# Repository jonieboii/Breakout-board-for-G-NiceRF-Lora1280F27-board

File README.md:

# Legal Disclaimer:
USER BEWARE. This is a simple breakout board created as an aid for my own prototyping purposes. 
Not withstanding the preceding and the above, DOWNLOAD, OR USE **SOLELY AT YOUR OWN RISK**. 
No warranty or representation is offered, nor should any be implied, of any kind, whatsoever. 
It is the end user's responsibility to determine suitability for their needs, and it is the end user's responsibility to test accordingly. 
Be sure to comply with all applicable rules and regulations that may govern its possession or use, which may vary by country. 
No recommendation is being made that you use it. No assistance is promised, nor should any assistance be assumed. 
No updates or corrections are promised, nor should any updates or corrections be assumed.

# G-NiceRF LoRa1280F27 Breakout Board

This is a simple breakout board for the **G-NiceRF LoRa1280F27** 500mW 2.4GHz LoRa module. Please note that this breakout board is not for the  Lora1280F27-TCXO variant which is also produced by G-Nice RF.

## Features
I have Breaken out all 18 pins from the module to standard 2.54mm headers and included two decoupling capacitors (10uF and 100nF) near VCC for stable operation.
I also  did a  **50-ohm coplanar waveguide** trace for the antenna and has inlcuded footprint for a standard **U.FL connector** for easily connecting the antennas.
The module has a full ground plane on both the top and bottom layers with stitching vias for low noise . My appologies for the messy schematic.

## How to Use

* **For KiCad Users:** The full KiCad 9 project is in the `GNice-RF SX1280 F27 Project Files` folder. You must also add the libraries from the `Custom footprint and symbol` folder to your KiCad global libraries.
* **For Manufacturing:** A `GNiceRF SX1280 Gerbers for Fab.zip` file is provided. You can upload this file directly to any PCB manufacturer.

For pinout, refer to the official G-NiceRF LoRa1280F27 datasheet.

For more information ragarding the module, you can refer to the the datasheet: https://www.nicerf.com/lora-module/sx1280-lora-module-lora1280f27.html

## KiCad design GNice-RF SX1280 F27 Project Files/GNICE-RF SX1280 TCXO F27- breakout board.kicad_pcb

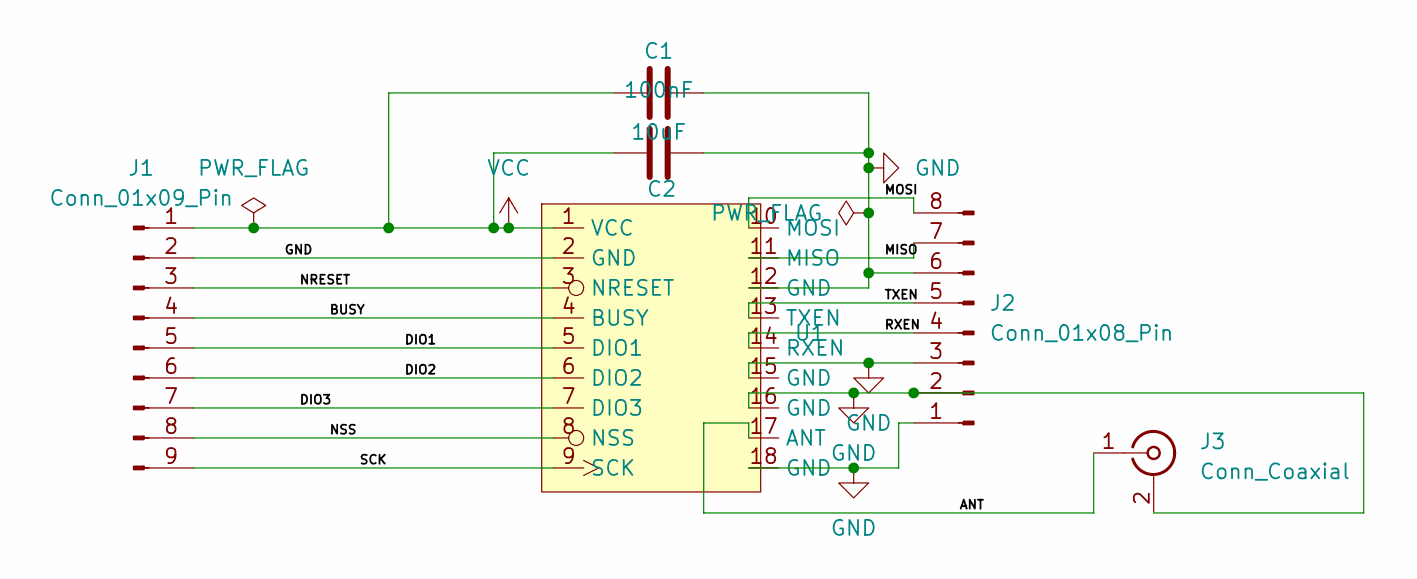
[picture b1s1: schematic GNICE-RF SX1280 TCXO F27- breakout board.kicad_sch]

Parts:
C1: 100nF; C_0805_2012Metric
C2: 10uF; C_0805_2012Metric
J1: Conn_01x09_Pin; PinHeader_1x09_P2.54mm_Vertical
J2: Conn_01x08_Pin; PinHeader_1x08_P2.54mm_Vertical
J3: Conn_Coaxial; U.FL_Hirose_U.FL-R-SMT-1_Vertical
U1: G-Nice RF SX1280-TCXO

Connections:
/ANT: J3.1 (In), U1.17 (ANT)
/BUSY: J1.4, U1.4 (BUSY)
/DIO1: J1.5, U1.5 (DIO1)
/DIO2: J1.6, U1.6 (DIO2)
/DIO3: J1.7, U1.7 (DIO3)
/MISO: J2.7, U1.11 (MISO)
/MOSI: J2.8, U1.10 (MOSI)
/NRESET: J1.3, U1.3 (NRESET)
/NSS: J1.8, U1.8 (NSS)
/RXEN: J2.4, U1.14 (RXEN)
/SCK: J1.9, U1.9 (SCK)
/TXEN: J2.5, U1.13 (TXEN)
GND: C1.1, C2.1, J1.2, J2.1, J2.2, J2.3, J2.6, J3.2 (Ext), U1.2 (GND), U1.12 (GND), U1.15 (GND), U1.16 (GND), U1.18 (GND)
VCC: C1.2, C2.2, J1.1, U1.1 (VCC)

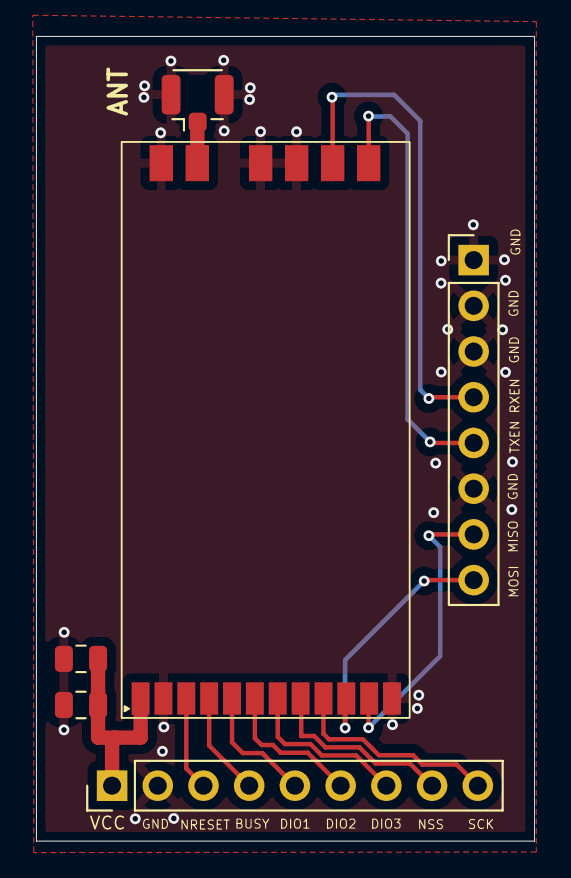
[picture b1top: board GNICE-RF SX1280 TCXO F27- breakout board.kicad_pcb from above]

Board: 2 copper layers, 27.7 x 44.7 mm, 6 parts (0 on the bottom side), 14 nets.

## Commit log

2025-11-07 Add README with legal disclaimer and board details
    Added legal disclaimer and detailed information about the G-NiceRF LoRa1280F27 breakout board, including features and usage instructions.
2025-11-10 Fix typos in README.md
    Corrected typos and improved clarity in the README.
